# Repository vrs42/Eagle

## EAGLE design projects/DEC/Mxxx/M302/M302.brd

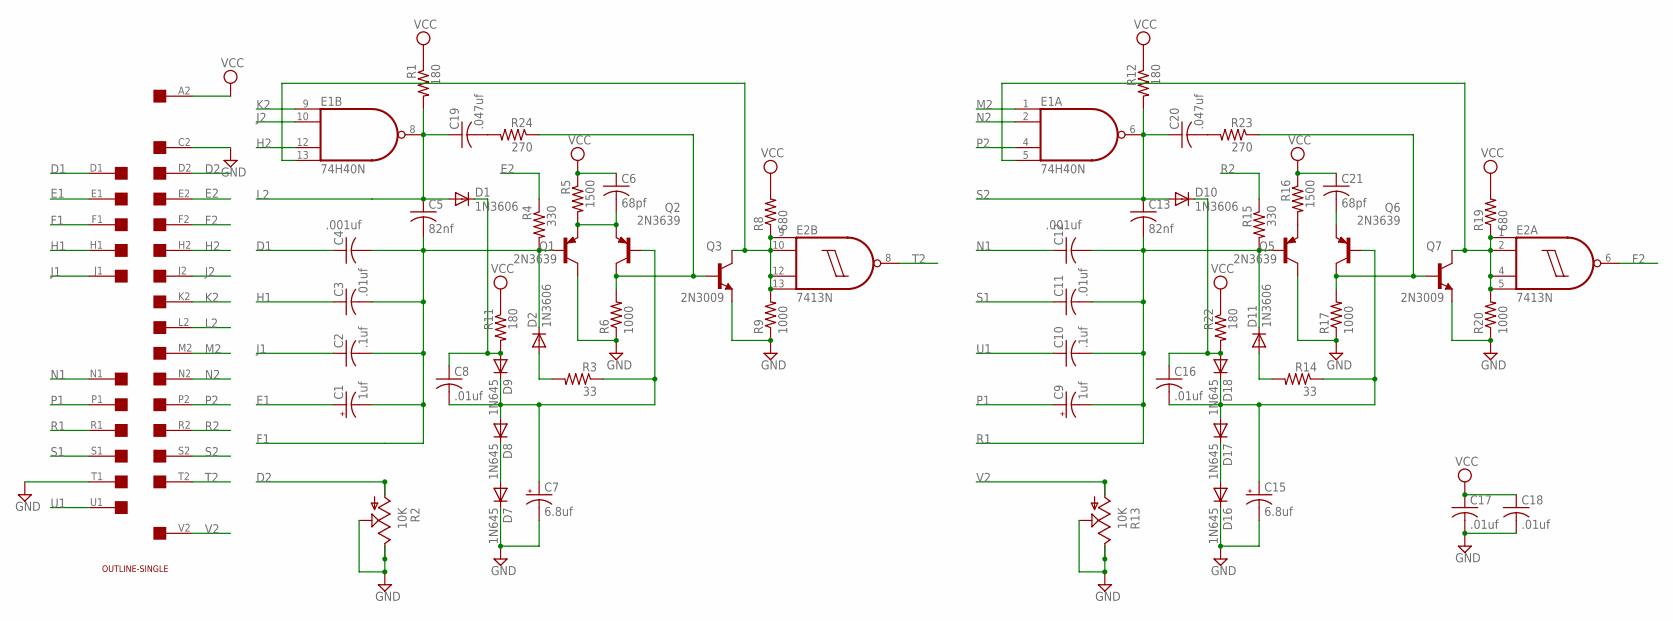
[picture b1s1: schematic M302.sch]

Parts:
C1, C9: 1uf; E15-5
C2, C10: .1uf; C050-025X075
C3, C8, C11, C16, C17, C18: .01uf; C050-025X075
C4, C12: .001uf; C050-025X075
C5, C13: 82nf; C050-025X075
C6, C21: 68pf; C050-025X075
C7, C15: 6.8uf; E15-5
C19, C20: .047uf; C050-025X075
D1, D2, D10, D11: 1N3606; DO35-10
D7, D8, D9, D16, D17, D18: 1N645; DO35-10
E1: 74H40N; DIL14
E2: 7413N; DIL14
Q1, Q2, Q5, Q6: 2N3639; TO39
Q3, Q7: 2N3009; TO39
R1, R11, R12, R22: 180; 0207/10
R2, R13: 10K; PT-SPIN
R3, R14: 33; 0207/10
R4, R15: 330; 0207/10
R5, R16: 1500; 0207/10
R6, R9, R17, R20: 1000; 0207/10
R8, R19: 680; 0207/10
R23, R24: 270; 0207/10
U$1: SINGLE; EDGE-CON2
U$2: OUTLINE-SINGLE; SINGLE

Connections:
D1: C4.1, U$1.D1
D2: R2.A, U$1.D2
E1: C1.+, U$1.E1
E2: R4.1, U$1.E2
F1: C1.-, C2.2, C3.2, C4.2, C5.2, D2.C, Q1.2 (B), R4.2, U$1.F1
F2: E2.6 (O), U$1.F2
GND: C7.-, C15.-, C17.2, C18.2, D7.C, D16.C, E1.7 (GND), E2.7 (GND), Q1.3 (C), Q3.1 (E), Q5.3 (C), Q7.1 (E), R2.E, R2.S, R6.1, R9.1, R13.E, R13.S, R17.1, R20.1, U$1.C2, U$1.T1
H1: C3.1, U$1.H1
H2: E1.12 (I2), U$1.H2
J1: C2.1, U$1.J1
J2: E1.10 (I1), U$1.J2
K2: E1.9 (I0), U$1.K2
L2: C5.1, C19.1, D1.A, E1.8 (O), R1.2, U$1.L2
M2: E1.1 (I0), U$1.M2
N1: C12.1, U$1.N1
N2: E1.2 (I1), U$1.N2
unnamed: C8.1, D1.C, D9.A, R11.2
unnamed: E1.13 (I3), E2.9 (I0), E2.10 (I1), E2.12 (I2), E2.13 (I3), Q3.3 (C), R8.1, R9.2
unnamed: C6.2, Q1.1 (E), Q2.1 (E), R5.2
unnamed: E1.5 (I3), E2.1 (I0), E2.2 (I1), E2.4 (I2), E2.5 (I3), Q7.3 (C), R19.1, R20.2
unnamed: C7.+, C8.2, D8.A, D9.C, Q2.2 (B), R3.1
unnamed: Q6.3 (C), Q7.2 (B), R17.2, R23.1
unnamed: D2.A, R3.2
unnamed: Q2.3 (C), Q3.2 (B), R6.2, R24.1
unnamed: D7.A, D8.C
unnamed: Q5.1 (E), R16.2
unnamed: C21.2, Q6.1 (E)
unnamed: C15.+, C16.2, D17.A, D18.C, Q6.2 (B), R14.1
unnamed: D11.A, R14.2
unnamed: C19.2, R24.2
unnamed: C20.2, R23.2
unnamed: C16.1, D10.C, D18.A, R22.2
unnamed: D16.A, D17.C
P1: C9.+, U$1.P1
P2: E1.4 (I2), U$1.P2
R1: C9.-, C10.2, C11.2, C12.2, C13.2, D11.C, Q5.2 (B), R15.2, U$1.R1
R2: R15.1, U$1.R2
S1: C11.1, U$1.S1
S2: C13.1, C20.1, D10.A, E1.6 (O), R12.2, U$1.S2
T2: E2.8 (O), U$1.T2
U1: C10.1, U$1.U1
V2: R13.A, U$1.V2
VCC: C6.1, C17.1, C18.1, C21.1, E1.14 (VCC), E2.14 (VCC), R1.1, R5.1, R8.2, R11.1, R12.1, R16.1, R19.2, R22.1, U$1.A2

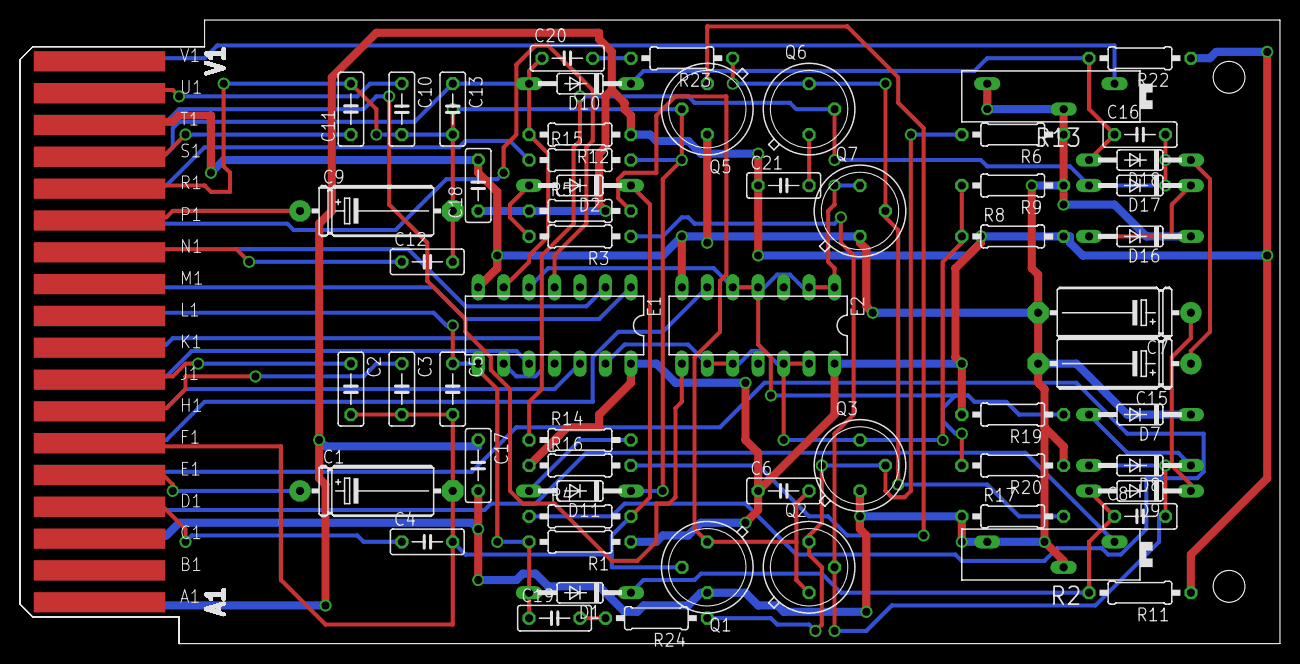
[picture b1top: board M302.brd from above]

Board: 2 copper layers, 125.7 x 62.2 mm, 60 parts (0 on the bottom side), 43 nets.

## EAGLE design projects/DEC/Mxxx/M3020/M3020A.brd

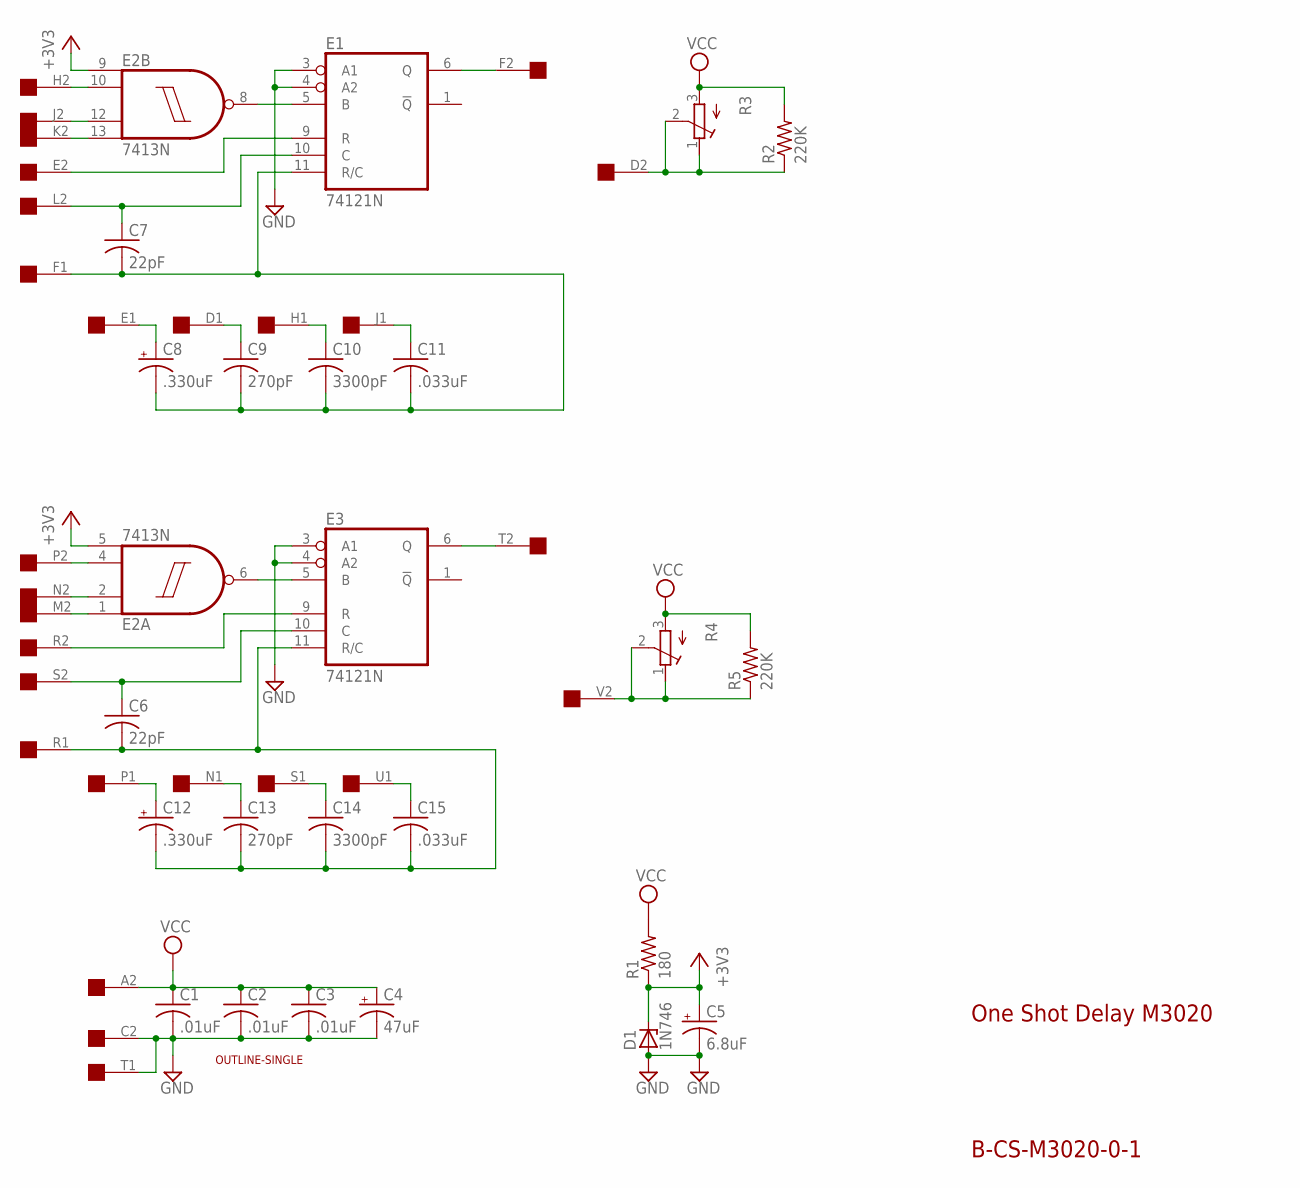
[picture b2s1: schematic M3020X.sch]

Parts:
C1, C2, C3: .01uF; C050-025X075
C4: 47uF; E12-8
C5: 6.8uF; E12-8
C6, C7: 22pF; C050-025X075
C8, C12: .330uF; E15-5
C9, C13: 270pF; C075-032X103
C10, C14: 3300pF; C102-043X133
C11, C15: .033uF; C225-062X268
D1: 1N746; DO35Z10
E1, E3: 74121N; DIL14
E2: 7413N; DIL14
R1: 180; 0207/10
R2, R5: 220K; 0207/10
R3, R4: 275P; 3006Y
U$1: OUTLINE-SINGLE; SINGLE
U$2: SINGLE; EDGE-CON2

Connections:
+3V3: C5.+, D1.C, E2.5 (I3), E2.9 (I0), R1.1
D1: C9.1, U$2.D1
D2: R2.1, R3.1 (A), R3.2 (S), U$2.D2
E1: C8.+, U$2.E1
E2: E1.9 (R), U$2.E2
F1: C7.2, C8.-, C9.2, C10.2, C11.2, E1.11 (R/C), U$2.F1
F2: E1.6 (Q), U$2.F2
GND: C1.2, C2.2, C3.2, C4.-, C5.-, D1.A, E1.3 (A1), E1.4 (A2), E1.7 (GND), E2.7 (GND), E3.3 (A1), E3.4 (A2), E3.7 (GND), U$2.C2, U$2.T1
H1: C10.1, U$2.H1
H2: E2.10 (I1), U$2.H2
J1: C11.1, U$2.J1
J2: E2.12 (I2), U$2.J2
K2: E2.13 (I3), U$2.K2
L2: C7.1, E1.10 (C), U$2.L2
M2: E2.1 (I0), U$2.M2
N1: C13.1, U$2.N1
N2: E2.2 (I1), U$2.N2
unnamed: E2.6 (O), E3.5 (B)
unnamed: E1.5 (B), E2.8 (O)
P1: C12.+, U$2.P1
P2: E2.4 (I2), U$2.P2
R1: C6.2, C12.-, C13.2, C14.2, C15.2, E3.11 (R/C), U$2.R1
R2: E3.9 (R), U$2.R2
S1: C14.1, U$2.S1
S2: C6.1, E3.10 (C), U$2.S2
T2: E3.6 (Q), U$2.T2
U1: C15.1, U$2.U1
V2: R4.1 (A), R4.2 (S), R5.1, U$2.V2
VCC: C1.1, C2.1, C3.1, C4.+, E1.14 (VCC), E2.14 (VCC), E3.14 (VCC), R1.2, R2.2, R3.3 (E), R4.3 (E), R5.2, U$2.A2

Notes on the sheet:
B-CS-M3020-0-1
One Shot Delay M3020

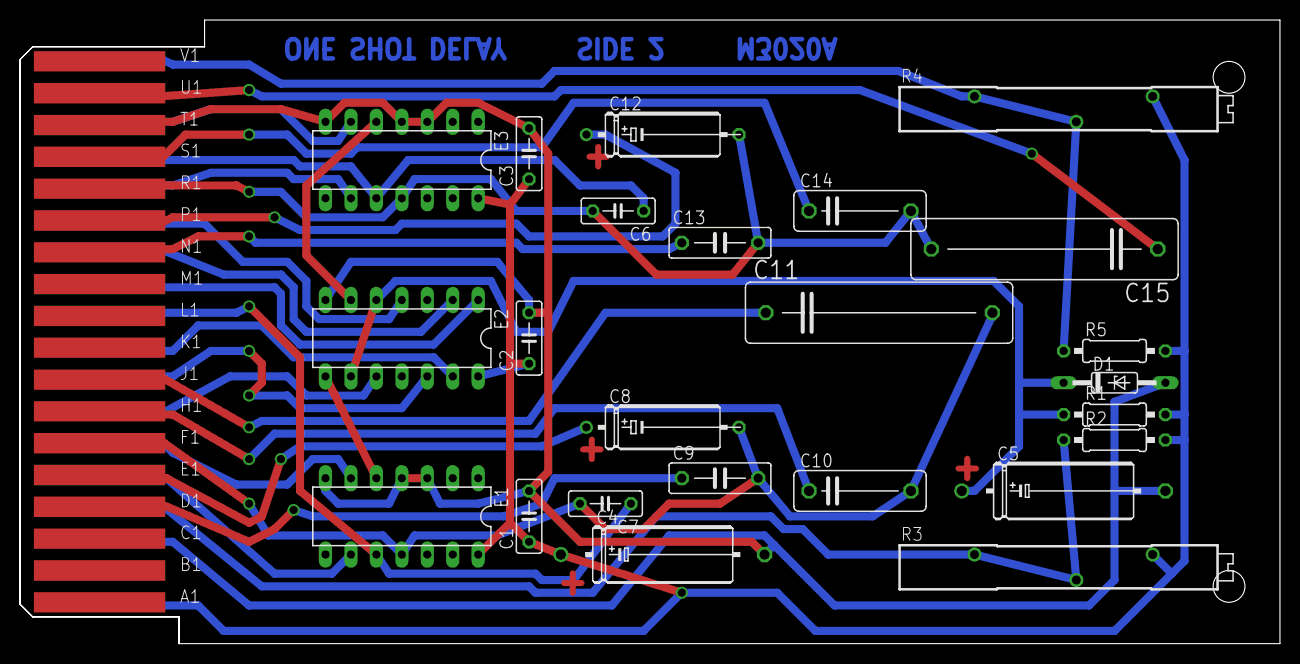
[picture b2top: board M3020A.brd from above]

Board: 2 copper layers, 125.7 x 62.2 mm, 26 parts (0 on the bottom side), 29 nets.

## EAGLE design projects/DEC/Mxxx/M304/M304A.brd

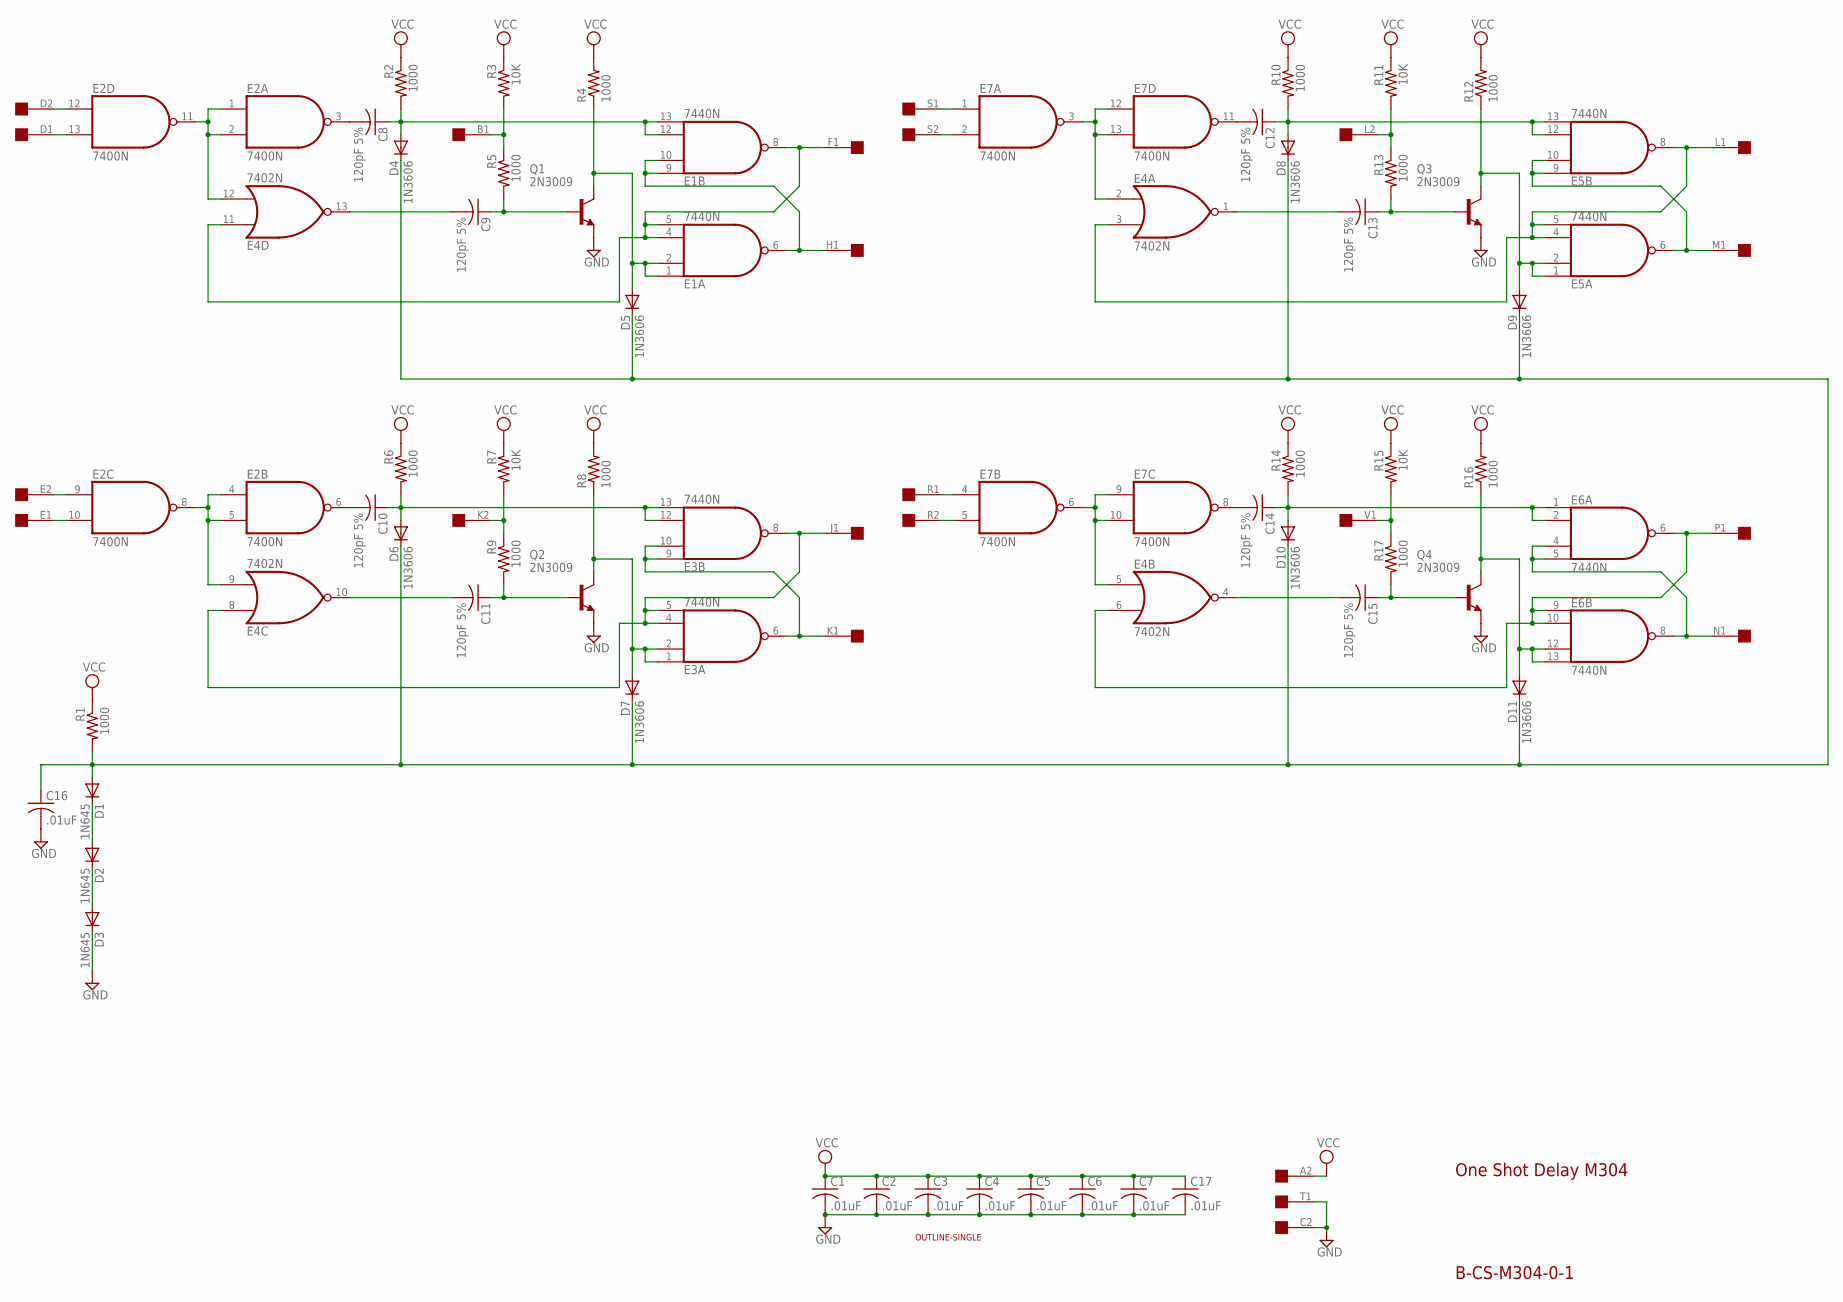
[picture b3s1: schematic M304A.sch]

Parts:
C1, C2, C3, C4, C5, C6, C7, C16, C17: .01uF; C050-025X075
C8, C9, C10, C11, C12, C13, C14, C15: 120pF 5%; C050-025X075
D1, D2, D3: 1N645; DO35-10
D4, D5, D6, D7, D8, D9, D10, D11: 1N3606; DO35-10
E1, E3, E5, E6: 7440N; DIL14
E2, E7: 7400N; DIL14
E4: 7402N; DIL14
Q1, Q2, Q3, Q4: 2N3009; TO39
R1, R2, R4, R5, R6, R8, R9, R10, R12, R13, R14, R16, R17: 1000; 0207/10
R3, R7, R11, R15: 10K; 0207/10
U$1: SINGLE; EDGE-CON2
U$2: OUTLINE-SINGLE; SINGLE

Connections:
GND: C1.2, C2.2, C3.2, C4.2, C5.2, C6.2, C7.2, C16.2, C17.2, D3.C, E1.7 (GND), E2.7 (GND), E3.7 (GND), E4.7 (GND), E5.7 (GND), E6.7 (GND), E7.7 (GND), Q1.1 (E), Q2.1 (E), Q3.1 (E), Q4.1 (E), U$1.C2, U$1.T1
unnamed: C16.1, D1.A, D4.C, D5.C, D6.C, D7.C, D8.C, D9.C, D10.C, D11.C, R1.2
unnamed: D5.A, E1.1 (I0), E1.2 (I1), Q1.3 (C), R4.1
unnamed: E2.1 (I0), E2.2 (I1), E2.11 (O), E4.12 (I1)
unnamed: E2.13 (I1), U$1.D1
unnamed: D1.C, D2.A
unnamed: E2.12 (I0), U$1.D2
unnamed: C8.2, E2.3 (O)
unnamed: C8.1, D4.A, E1.12 (I2), E1.13 (I3), R2.2
unnamed: D2.C, D3.A
unnamed: C9.2, E4.13 (O)
unnamed: C9.1, Q1.2 (B), R5.2
unnamed: R3.2, R5.1, U$1.B1
unnamed: E1.4 (I2), E1.5 (I3), E1.8 (O), E4.11 (I0), U$1.F1
unnamed: E1.6 (O), E1.9 (I0), E1.10 (I1), U$1.H1
unnamed: D7.A, E3.1 (I0), E3.2 (I1), Q2.3 (C), R8.1
unnamed: E2.4 (I0), E2.5 (I1), E2.8 (O), E4.9 (I1)
unnamed: E2.9 (I0), U$1.E2
unnamed: E2.10 (I1), U$1.E1
unnamed: C10.2, E2.6 (O)
unnamed: C10.1, D6.A, E3.12 (I2), E3.13 (I3), R6.2
unnamed: C11.2, E4.10 (O)
unnamed: C11.1, Q2.2 (B), R9.2
unnamed: R7.2, R9.1, U$1.K2
unnamed: E3.4 (I2), E3.5 (I3), E3.8 (O), E4.8 (I0), U$1.J1
unnamed: E3.6 (O), E3.9 (I0), E3.10 (I1), U$1.K1
unnamed: D9.A, E5.1 (I0), E5.2 (I1), Q3.3 (C), R12.1
unnamed: E4.2 (I0), E7.3 (O), E7.12 (I0), E7.13 (I1)
unnamed: E7.1 (I0), U$1.S1
unnamed: E7.2 (I1), U$1.S2
unnamed: C12.2, E7.11 (O)
unnamed: C12.1, D8.A, E5.12 (I2), E5.13 (I3), R10.2
unnamed: C13.2, E4.1 (O)
unnamed: C13.1, Q3.2 (B), R13.2
unnamed: R11.2, R13.1, U$1.L2
unnamed: E4.3 (I1), E5.4 (I2), E5.5 (I3), E5.8 (O), U$1.L1
unnamed: E5.6 (O), E5.9 (I0), E5.10 (I1), U$1.M1
unnamed: D11.A, E6.12 (I2), E6.13 (I3), Q4.3 (C), R16.1
unnamed: E4.5 (I0), E7.6 (O), E7.9 (I0), E7.10 (I1)
unnamed: E7.4 (I0), U$1.R1
unnamed: E7.5 (I1), U$1.R2
unnamed: C14.2, E7.8 (O)
unnamed: C14.1, D10.A, E6.1 (I0), E6.2 (I1), R14.2
unnamed: C15.2, E4.4 (O)
unnamed: C15.1, Q4.2 (B), R17.2
unnamed: R15.2, R17.1, U$1.V1
unnamed: E4.6 (I1), E6.6 (O), E6.9 (I0), E6.10 (I1), U$1.P1
unnamed: E6.4 (I2), E6.5 (I3), E6.8 (O), U$1.N1
VCC: C1.1, C2.1, C3.1, C4.1, C5.1, C6.1, C7.1, C17.1, E1.14 (VCC), E2.14 (VCC), E3.14 (VCC), E4.14 (VCC), E5.14 (VCC), E6.14 (VCC), E7.14 (VCC), R1.1, R2.1, R3.1, R4.2, R6.1, R7.1, R8.2, R10.1, R11.1, R12.2, R14.1, R15.1, R16.2, U$1.A2

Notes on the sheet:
One Shot Delay M304
B-CS-M304-0-1

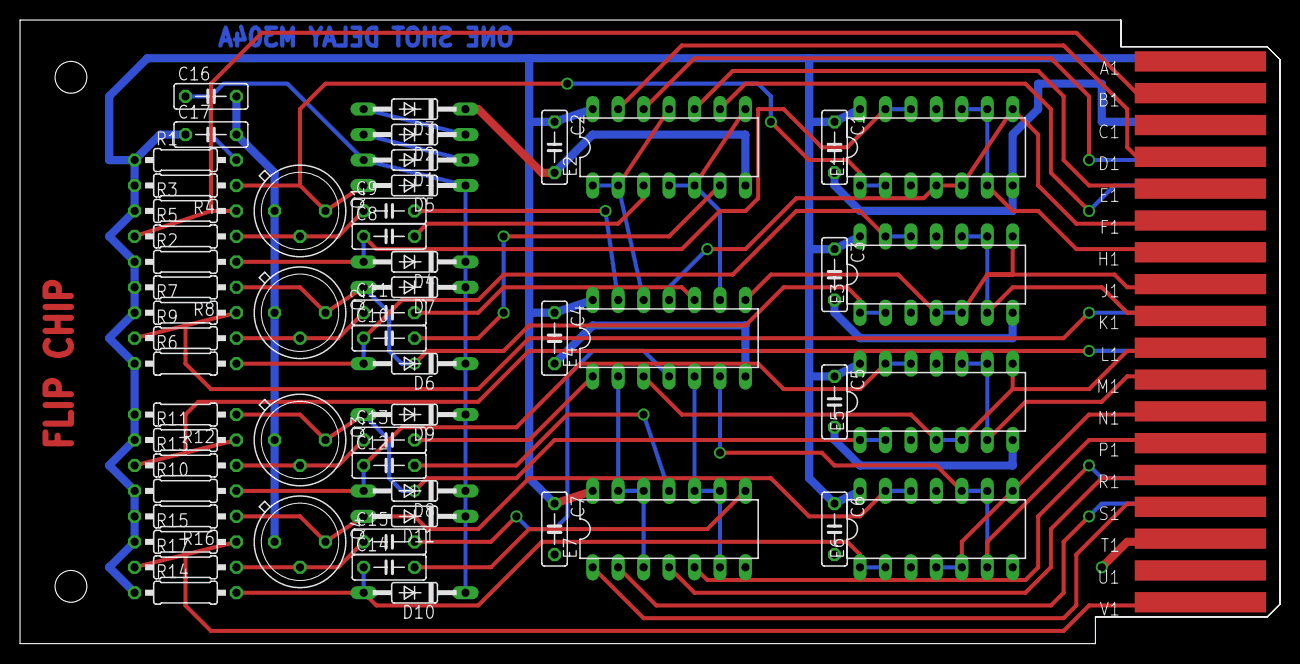
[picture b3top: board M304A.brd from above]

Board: 2 copper layers, 125.7 x 62.2 mm, 59 parts (0 on the bottom side), 49 nets.

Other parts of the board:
U$3: FLIPCHIP
